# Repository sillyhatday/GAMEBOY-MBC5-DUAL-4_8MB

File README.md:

# GAMEBOY-MBC5-DUAL-4/8MB

## 🟦 Introduction

A working 8MB Gameboy flash cart. It uses 2 flash chips to double the ROM storage space. It can be configured for 2x2MB or 2x4MB for 4MB or 8MB respectively.

If you are looking at this as your first flash cart, then I'd recommend you look at one of my other projects first, then make 20 of them. This is one of the more difficult flash carts to build.

You have all seen how much 4MB flash chips are vs the 2MB flash chips. You can buy two 2MB chips for less than one 4MB chip. So why can’t you use them together to make 4MB? Well you can now with a little bit of basic logic. Even with the logic chip it is still cheaper than one 4MB chip, but the more of these you make, the cheaper each cart works out.

The cost per cart is directly between making an ordinary 2MB cart and a 4MB cart. There is zero downsides or quirks to this, it just works. You will have to use its own FlashGBX profile as it doesn’t auto detect, but that’s it. ~~Maybe Lesserkuma will include even it in a newer version to make it even more seamless.~~ 

>[!NOTE]
>UPDATE! As of V3.30 it is included!

Only one game was ever released to use all 8MB. I imagine the cart cost and coding time to track so many ROM banks wasn't worth it to everyone. So if you really wish to play Desnha De Go 2, then this is for you. A Japanese train simulator. This obviously requires 2 expensive 4MB flash chips. I guess you really got to want it. On a more serious note, the more accessible an 8MB cartridge is, the more likely people will develop games or ROM hacks for that size of cartridge. I think the main use for this right now is the video ROMs out there.

>[!TIP]
>When building your cartridge you just have to put a solder bridge over the desired 4 or 8MB jumper. Also many <2MB MBC5 games, they don’t require the additional glue logic for FRAM. For whatever reason, all 4MB ROMs tested require some extra glue logic.

## Game compatibility
Simply put this cart has the best compatibility of all my cartridges. If you want a cartridge that has the least compromises, this is the one.

Nearly all Gameboy colour games used this memory mapper. It can address 32KB to 8MB of game storage and 8KB to 128KB of game save storage. This one can use all 8MB of game storage and only 32KB of save storage. Most 8KB save files should work fine on the 32KB chip and I think only LSDJ uses 128KB of save storage.

Games that use real time clock functions do not work on this cartridge due to it not having the clock functionality. Most later Pokemon games will not work properly on this. They require a MBC3 cartridge.

>[!WARNING]
>Once more, if you don't know how to solder this sort of thing then you should come back to this later. Don't be mad at me, I don't want you to waste your money.

## 🟦 Parts List

>[!IMPORTANT]
>When ordering cartridge PCBs, make sure to choose 0.8mm thickness and gold plating. <br>
>Order FRAM from Aliexpress & eBay at your own risk, they are known to be ***extremely*** unreliable. <br>

| Part | Quantity |
|------|----------|
| MBC5 | 1 |
| FM18W08 | 1 |
| 74LVC1G139 | 1 |
| 74LVC1G332GW125 | 1 |
| 29F016* | 2 |
| Capacitor 100nF | 5 |
| Resistor 10K | 2 |

*You can use a varity of flash chips for this. AM29F016B, MBM29F016, AM29F032, MBM29F033C for example, so long as they have the same pin out.

>[!NOTE]
>Flash the cartridge with the "Sillyhatday MBC5-DUAL-FLASH-4/8MB" profile in FlashGBX. The regular 4MB profiles will not work.

### Final version in 2x2MB config

### 2x2MB mode prototype

### 2x4MB mode prototype

## 💙 Thanks
Thanks to Jamo for helping test this prototype, Lesserkuma who helped setup FlashGBX and Modded Gameboy Gameboy Club for even giving me the idea in the first place.

## 🩷 Links

🖇️ Bytendo Mods GitHub: https://github.com/bytendomods <br>
🛒 Natalie Shop: https://nataliethenerd.com/ <br>
🤓 Natalie GitHub: https://github.com/natalie-lang/natalie <br>
📱 MGGC Discord: https://discord.gg/moddedgameboyclub

## License

This work is licensed under a Creative Commons Attribution-ShareAlike 4.0 International License. You are able to copy and redistribute the material in any medium or format, as well as remix, transform, or build upon the material for any purpose (even commercial) - but you must give appropriate credit, provide a link to the license, and indicate if any changes were made.

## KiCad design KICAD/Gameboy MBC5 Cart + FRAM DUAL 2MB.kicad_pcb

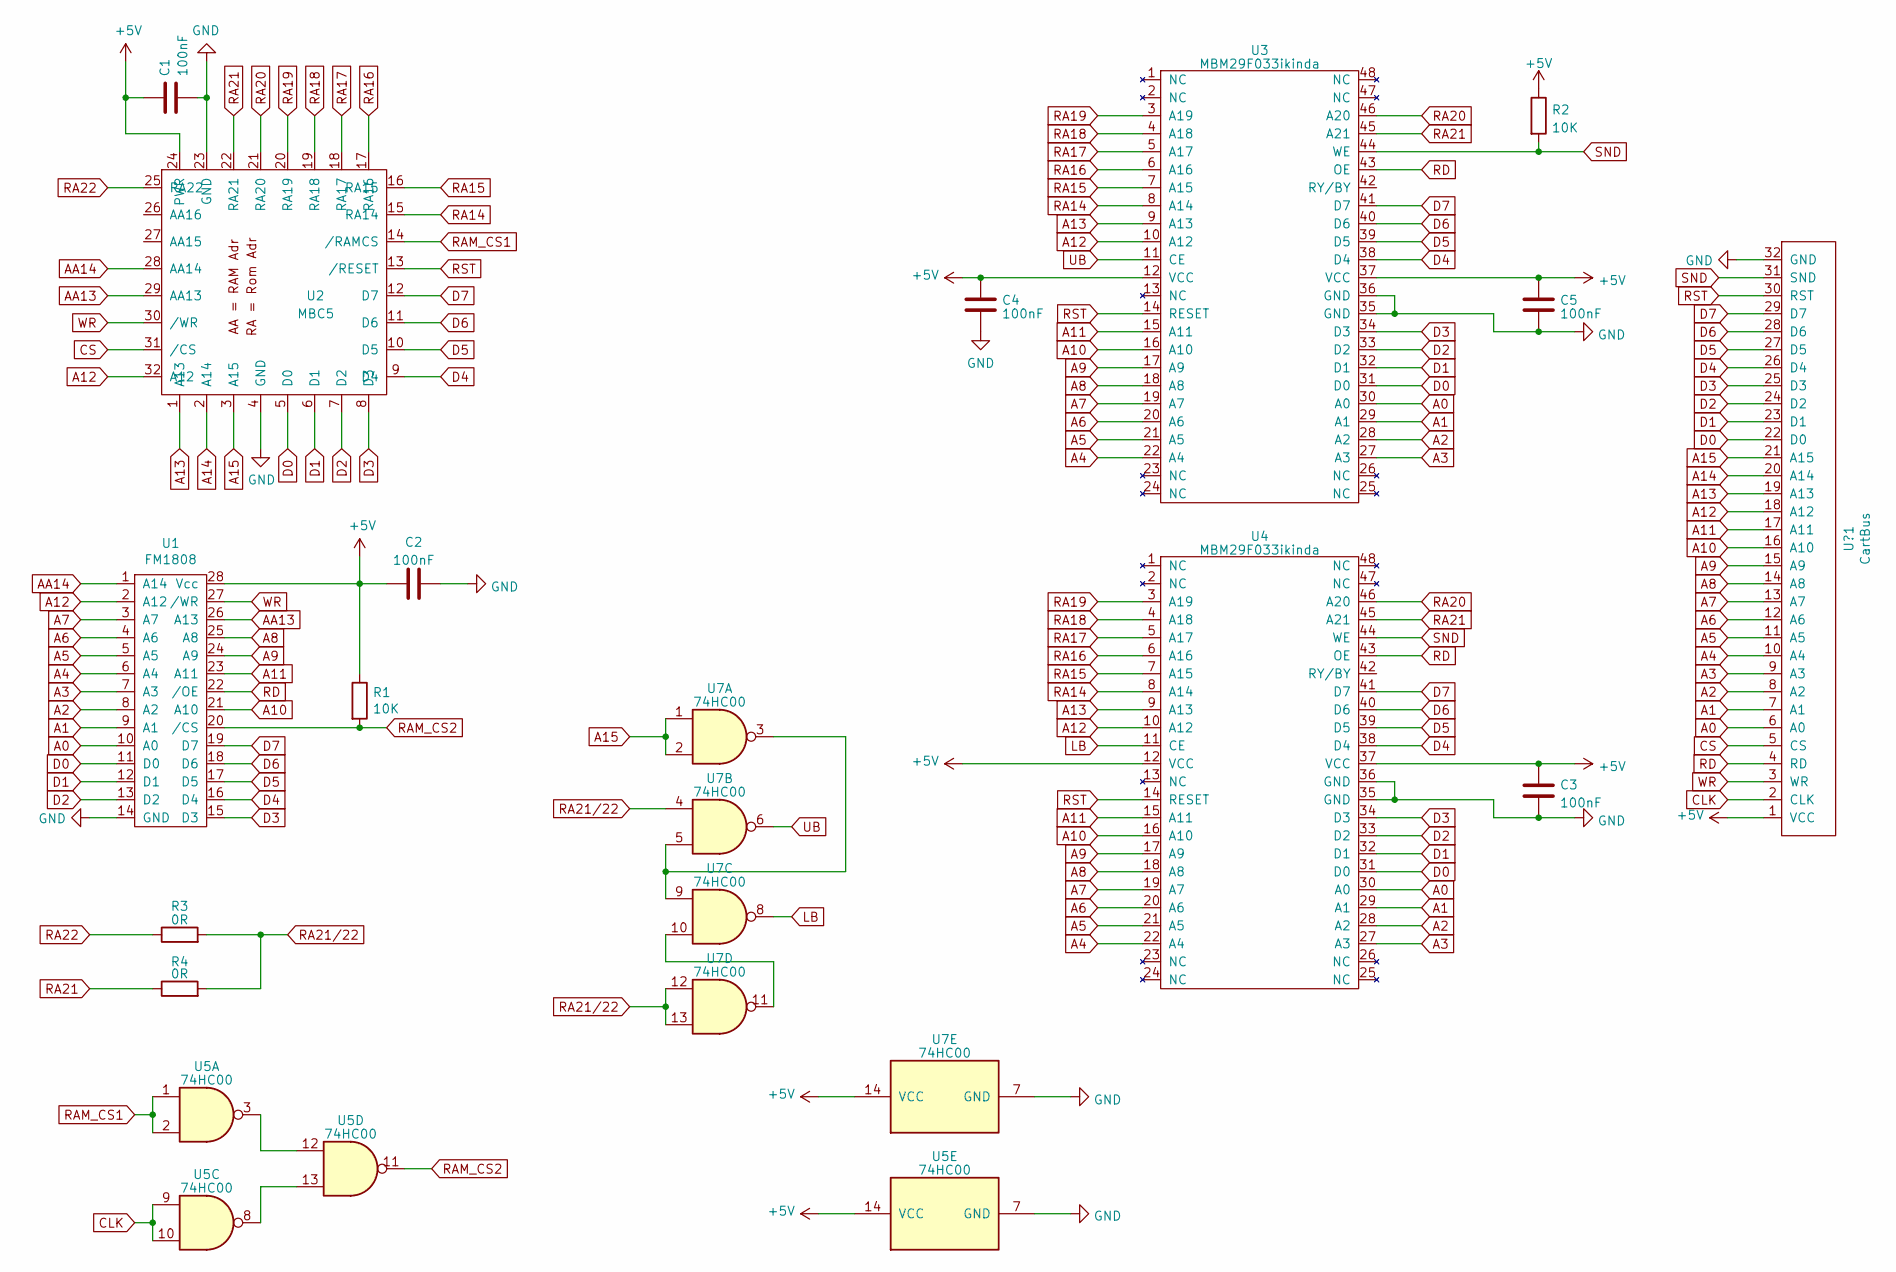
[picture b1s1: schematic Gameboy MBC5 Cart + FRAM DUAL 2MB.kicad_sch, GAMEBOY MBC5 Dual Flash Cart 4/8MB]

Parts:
C1, C2, C3, C4, C5: 100nF; C_0603_1608Metric_Pad1.08x0.95mm_HandSolder
R1, R2: 10K; R_0603_1608Metric_Pad0.98x0.95mm_HandSolder
R3, R4: 0R; LINK
U1: FM1808; SOIC-28W_7.5x17.9mm_P1.27mm
U2: MBC5; LQFP-32_7x7mm_P0.8mm
U3, U4: MBM29F033ikinda; MBM29F033-29F016
U5, U7: 74HC00; SO-14_3.9x8.65mm_P1.27mm
U?1: CartBus; GameBoy_GamePak_CGB-002_P1.50mm_Edge

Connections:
+5V: C1.1, C2.1, C3.1, C4.1, C5.1, R1.1, R2.1, U1.28 (Vcc), U2.24 (PWR), U3.12 (VCC), U3.37 (VCC~), U4.12 (VCC), U4.37 (VCC~), U5.14 (VCC), U7.14 (VCC), U?1.1 (VCC)
A0: U1.10 (A0), U3.30 (A0~), U4.30 (A0~), U?1.6 (A0)
A1: U1.9 (A1), U3.29 (A1), U4.29 (A1), U?1.7 (A1)
A2: U1.8 (A2), U3.28 (A2), U4.28 (A2), U?1.8 (A2)
A3: U1.7 (A3), U3.27 (A3), U4.27 (A3), U?1.9 (A3)
A4: U1.6 (A4), U3.22 (A4), U4.22 (A4), U?1.10 (A4)
A5: U1.5 (A5), U3.21 (A5), U4.21 (A5), U?1.11 (A5)
A6: U1.4 (A6), U3.20 (A6), U4.20 (A6), U?1.12 (A6)
A7: U1.3 (A7), U3.19 (A7), U4.19 (A7), U?1.13 (A7)
A8: U1.25 (A8), U3.18 (A8), U4.18 (A8), U?1.14 (A8)
A9: U1.24 (A9), U3.17 (A9), U4.17 (A9), U?1.15 (A9)
A10: U1.21 (A10), U3.16 (A10), U4.16 (A10), U?1.16 (A10)
A11: U1.23 (A11), U3.15 (A11), U4.15 (A11), U?1.17 (A11)
A12: U1.2 (A12), U2.32 (A12), U3.10 (A12), U4.10 (A12), U?1.18 (A12)
A13: U2.1 (A13), U3.9 (A13), U4.9 (A13), U?1.19 (A13)
A14: U2.2 (A14), U?1.20 (A14)
A15: U2.3 (A15), U7.1, U7.2, U?1.21 (A15)
AA13: U1.26 (A13), U2.29 (AA13)
AA14: U1.1 (A14), U2.28 (AA14)
CLK: U5.9, U5.10, U?1.2 (CLK~)
CS: U2.31 (/CS), U?1.5 (CS)
D0: U1.11 (D0), U2.5 (D0), U3.31 (D0), U4.31 (D0), U?1.22 (D0)
D1: U1.12 (D1), U2.6 (D1), U3.32 (D1), U4.32 (D1), U?1.23 (D1)
D2: U1.13 (D2), U2.7 (D2), U3.33 (D2), U4.33 (D2), U?1.24 (D2)
D3: U1.15 (D3), U2.8 (D3), U3.34 (D3), U4.34 (D3), U?1.25 (D3)
D4: U1.16 (D4), U2.9 (D4), U3.38 (D4), U4.38 (D4), U?1.26 (D4)
D5: U1.17 (D5), U2.10 (D5), U3.39 (D5), U4.39 (D5), U?1.27 (D5)
D6: U1.18 (D6), U2.11 (D6), U3.40 (D6), U4.40 (D6), U?1.28 (D6)
D7: U1.19 (D7), U2.12 (D7), U3.41 (D7), U4.41 (D7), U?1.29 (D7)
GND: C1.2, C2.2, C3.2, C4.2, C5.2, U1.14 (GND), U2.4 (GND), U2.23 (GND), U3.35 (GND), U3.36 (GND), U4.35 (GND), U4.36 (GND), U5.7 (GND), U7.7 (GND), U?1.32 (GND)
LB: U4.11 (CE), U7.8
unnamed: U5.3, U5.12
unnamed: U5.8, U5.13
unnamed: U7.3, U7.5, U7.9
unnamed: U7.10, U7.11
RA14: U2.15 (RA14), U3.8 (A14), U4.8 (A14)
RA15: U2.16 (RA15), U3.7 (A15), U4.7 (A15)
RA16: U2.17 (RA16), U3.6 (A16), U4.6 (A16)
RA17: U2.18 (RA17), U3.5 (A17), U4.5 (A17)
RA18: U2.19 (RA18), U3.4 (A18), U4.4 (A18)
RA19: U2.20 (RA19), U3.3 (A19), U4.3 (A19)
RA20: U2.21 (RA20), U3.46 (A20), U4.46 (A20)
RA21: R4.1, U2.22 (RA21), U3.45 (A21), U4.45 (A21)
RA21/22: R3.2, R4.2, U7.4, U7.12, U7.13
RA22: R3.1, U2.25 (RA22)
RAM_CS1: U2.14 (/RAMCS), U5.1, U5.2
RAM_CS2: R1.2, U1.20 (/CS), U5.11
RD: U1.22 (/OE), U3.43 (OE~), U4.43 (OE~), U?1.4 (RD)
RST: U2.13 (/RESET), U3.14 (RESET), U4.14 (RESET), U?1.30 (RST)
SND: R2.2, U3.44 (WE), U4.44 (WE), U?1.31 (SND)
UB: U3.11 (CE), U7.6
WR: U1.27 (/WR), U2.30 (/WR), U?1.3 (WR)

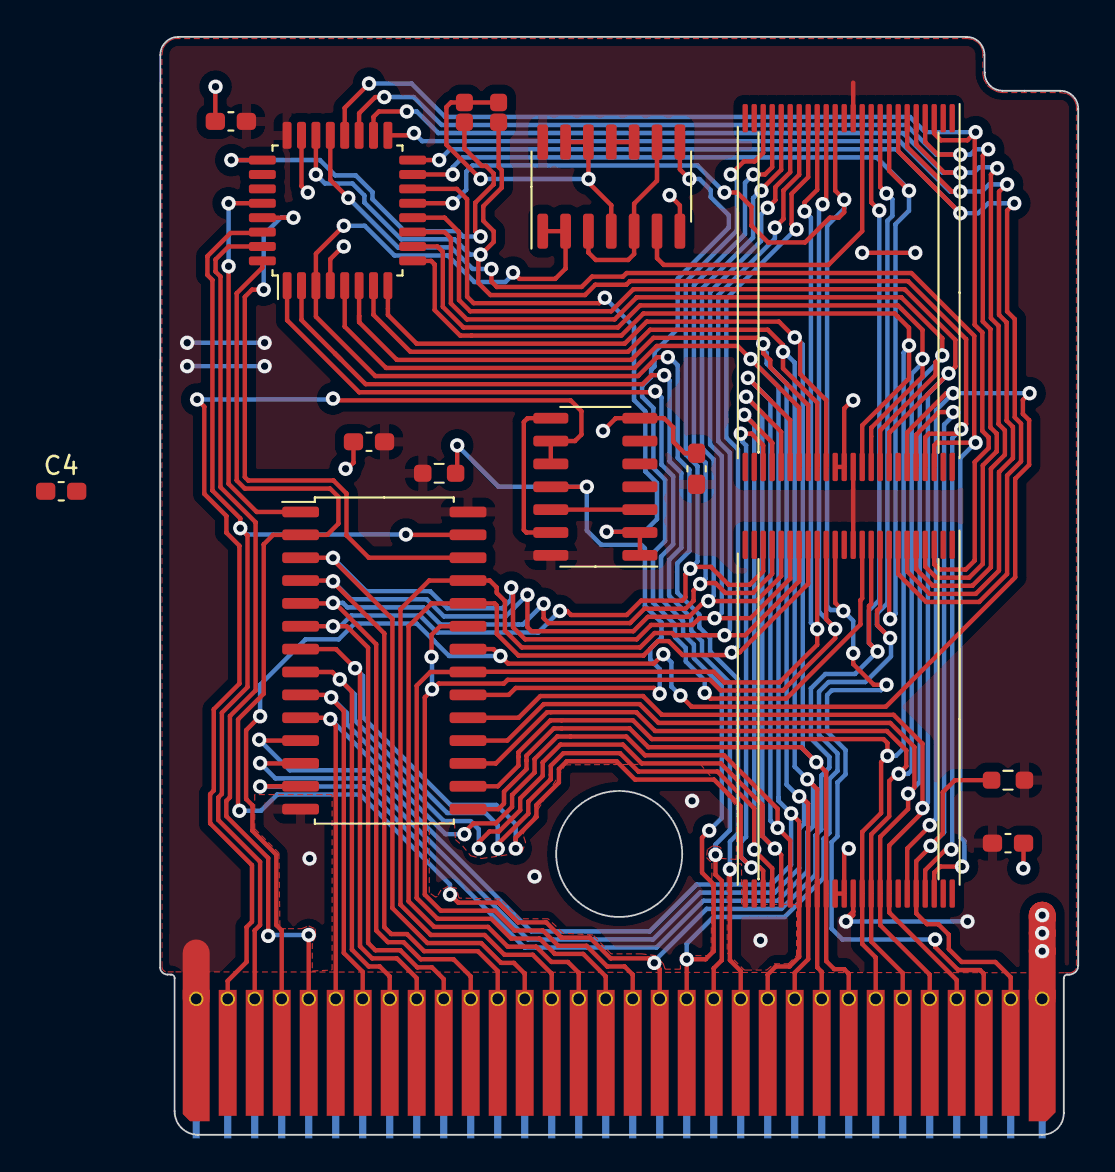
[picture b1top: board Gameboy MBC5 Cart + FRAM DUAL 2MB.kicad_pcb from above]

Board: 2 copper layers, 51.0 x 61.0 mm, 16 parts (0 on the bottom side), 52 nets.

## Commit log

2023-11-30 Delete fc_DMG_Sillyhatday_2x4_29F032_8MB.txt
    deleted useless 8mb GBXcart file
2023-12-14 Update README.md
    formatting
2023-12-31 Update README.md
    New photos
2024-01-02 Update README.md
    Added game compatibility section at the top of readme
2024-01-07 Update README.md
    Updated build guide as flashgbx already has my profile
2024-02-16 Update README.md
    Updated links at bottom of readme. Added extra instructions to build guide
2025-05-28 Create License.md
    added license
2025-05-28 Update README.md
    License added
2026-06-23 Update README.md
    Big readme update
2026-06-25 Create wen file
2026-06-25 Rename DUAL-FLASH-4-8MB-V1.0-NOJLC.rar to GERBERS/DUAL-FLASH-4-8MB-V1.0-NOJLC.rar
2026-06-25 Rename DUAL-FLASH-4-8MB-V1.0.rar to GERBERS/DUAL-FLASH-4-8MB-V1.0.rar
